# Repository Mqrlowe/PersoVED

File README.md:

# **Hello this is the ReadMe for my personnal github repo**

this repo contains mainly work for VED

### for the moment ts contains :
~~~
	PCB kicad projets
	CubeMx projetcs for the stm32
	A OneNote link to VED notes
~~~
### on the VED notes there is the following work :
~~~
	Can bus additionnal work to complete former studies
	regarding the can bus application in the FS architecture.
~~~

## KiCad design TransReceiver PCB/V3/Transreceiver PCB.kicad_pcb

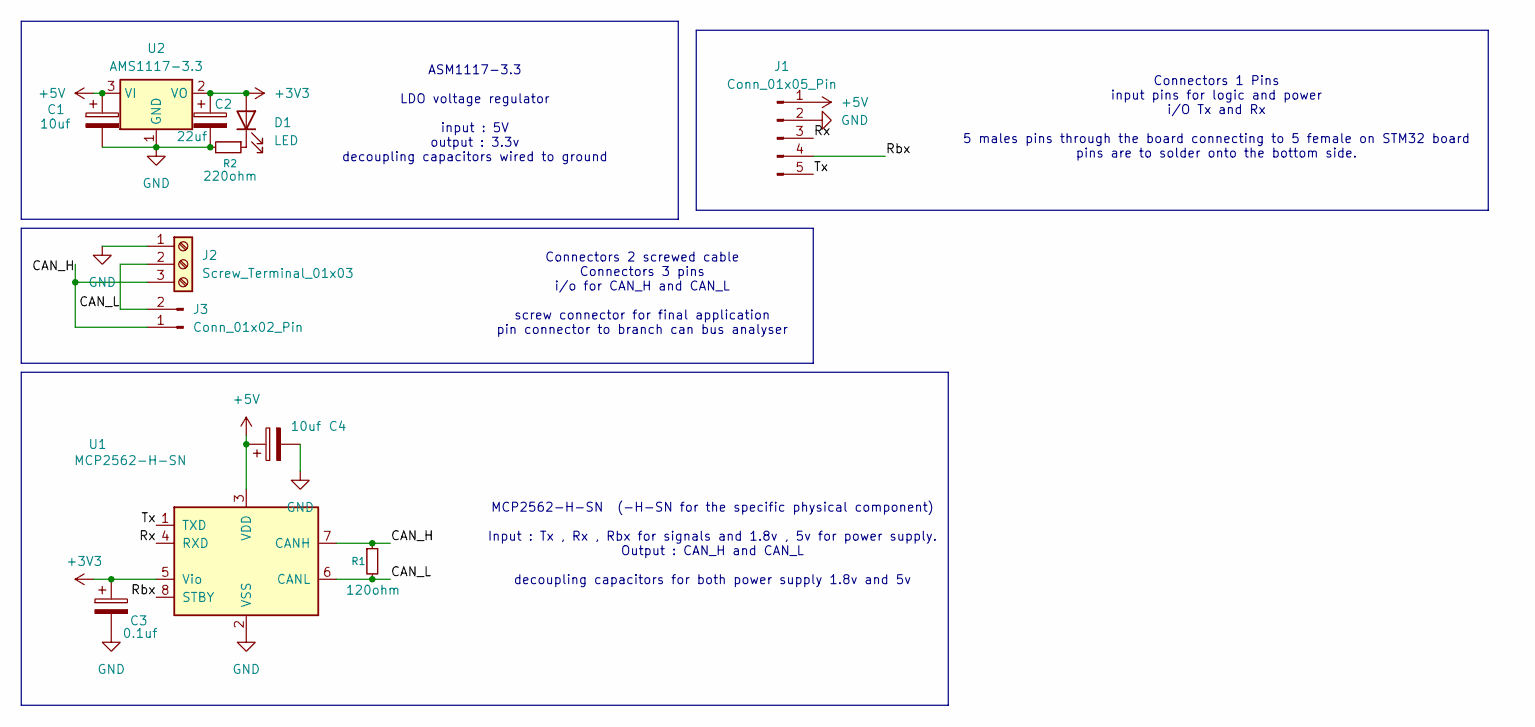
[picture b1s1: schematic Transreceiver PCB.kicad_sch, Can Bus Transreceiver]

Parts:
C1, C4: 10uf; C_0805_2012Metric
C2: 22uf; C_0805_2012Metric
C3: 0.1uf; C_0805_2012Metric
D1: LED; LED_0805_2012Metric
J1: Conn_01x05_Pin; PinHeader_1x05_P1.27mm_Horizontal
J2: Screw_Terminal_01x03; TerminalBlock_Phoenix_MKDS-1,5-3-5.08_1x03_P5.08mm_Horizont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
J3: Conn_01x02_Pin; PinHeader_1x02_P1.27mm_Vertical
R1: 120ohm; R_0805_2012Metric
R2: 220ohm; R_0805_2012Metric
U1: MCP2562-H-SN; SOIC-8_3.9x4.9mm_P1.27mm
U2: AMS1117-3.3; SOT-223-3_TabPin2

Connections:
+3V3: C2.1, C3.1, D1.2 (A), U1.5 (Vio), U2.2 (VO)
+5V: C1.1, C4.1, J1.1, U1.3 (VDD), U2.3 (VI)
/CAN_H: J2.3, J3.1, R1.1, U1.7 (CANH)
/CAN_L: J2.2, J3.2, R1.2, U1.6 (CANL)
/Rbx: J1.4, U1.8 (STBY)
/Rx: J1.3, U1.4 (RXD)
/Tx: J1.5, U1.1 (TXD)
GND: C1.2, C2.2, C3.2, C4.2, J1.2, J2.1, R2.2, U1.2 (VSS), U2.1 (GND)
unnamed: D1.1 (K), R2.1

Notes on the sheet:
ASM1117-3.3 LDO voltage regulator input : 5V output : 3.3v decoupling capacitors wired to ground
Connectors 2 screwed cable Connectors 3 pins i/o for CAN_H and CAN_L screw connector for final application pin connector to branch can bus analyser
MCP2562-H-SN (-H-SN for the specific physical component) Input : Tx , Rx , Rbx for signals and 1.8v , 5v for power supply. Output : CAN_H and CAN_L decoupling capacitors for both power supply 1.8v and 5v
Connectors 1 Pins input pins for logic and power i/O Tx and Rx 5 males pins through the board connecting to 5 female on STM32 board pins are to solder onto the bottom side.

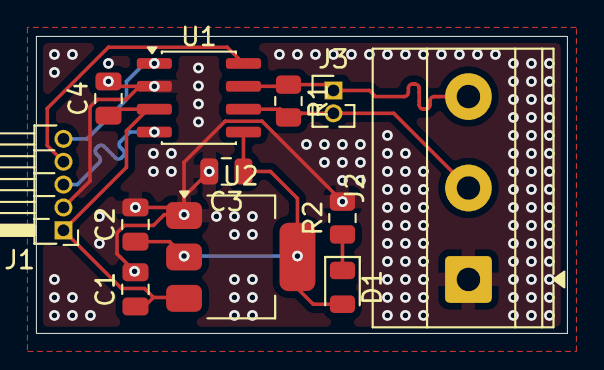
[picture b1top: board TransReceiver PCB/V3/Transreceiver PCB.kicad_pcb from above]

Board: 2 copper layers, 29.5 x 16.5 mm, 12 parts (0 on the bottom side), 9 nets.

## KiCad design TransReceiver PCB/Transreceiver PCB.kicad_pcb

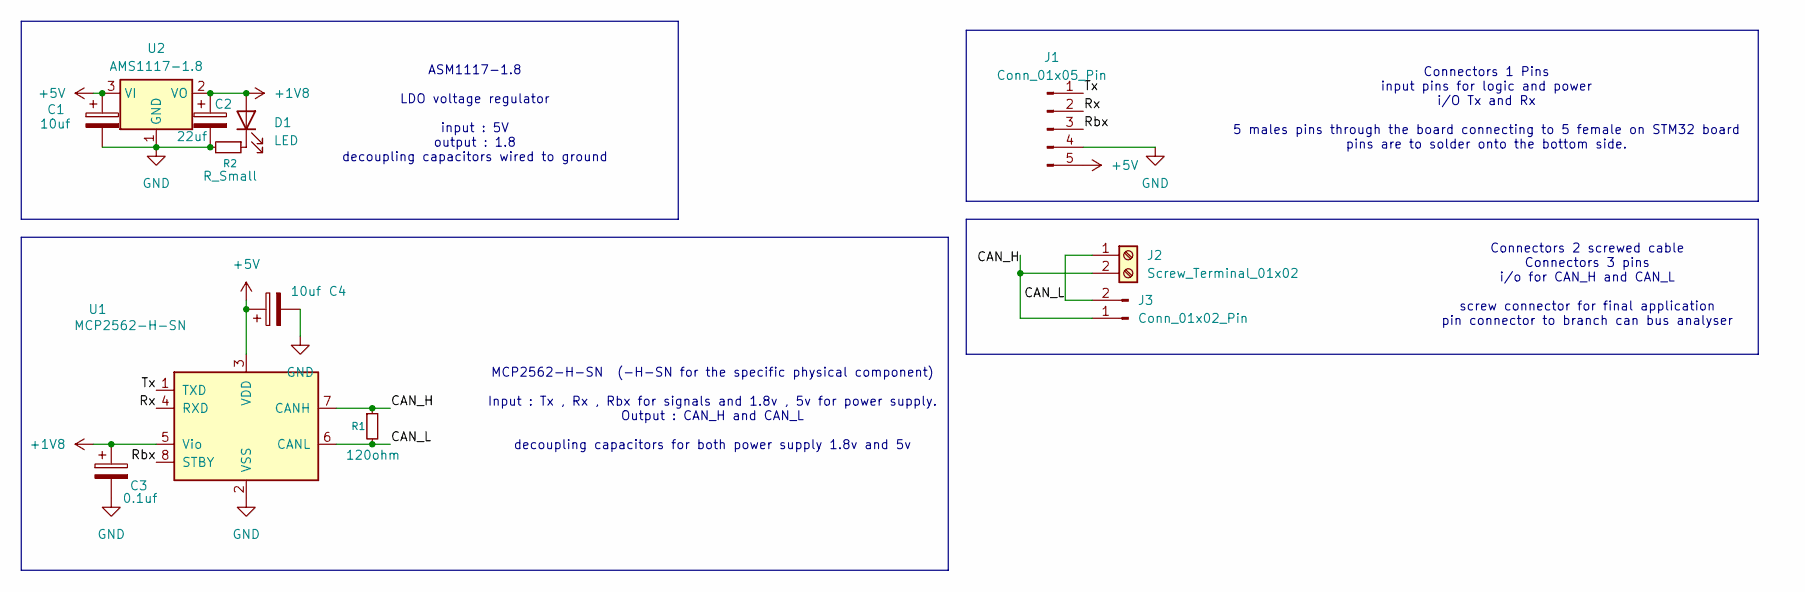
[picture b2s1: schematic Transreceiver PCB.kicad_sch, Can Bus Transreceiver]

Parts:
C1, C4: 10uf; C_0805_2012Metric
C2: 22uf; C_0805_2012Metric
C3: 0.1uf; C_0805_2012Metric
D1: LED; LED_0805_2012Metric
J1: Conn_01x05_Pin; PinHeader_1x05_P1.27mm_Vertical
J2: Screw_Terminal_01x02; TerminalBlock_Phoenix_PT-1,5-2-5.0-H_1x02_P5.00mm_Horizontal
J3: Conn_01x02_Pin; PinHeader_1x02_P1.27mm_Vertical
R1: 120ohm; R_0805_2012Metric
R2: R_Small; R_0805_2012Metric
U1: MCP2562-H-SN; SOIC-8_3.9x4.9mm_P1.27mm
U2: AMS1117-1.8; SOT-223-3_TabPin2

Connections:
+1V8: C2.1, C3.1, D1.2 (A), U1.5 (Vio), U2.2 (VO)
+5V: C1.1, C4.1, J1.5, U1.3 (VDD), U2.3 (VI)
/CAN_H: J2.2, J3.1, R1.1, U1.7 (CANH)
/CAN_L: J2.1, J3.2, R1.2, U1.6 (CANL)
/Rbx: J1.3, U1.8 (STBY)
/Rx: J1.2, U1.4 (RXD)
/Tx: J1.1, U1.1 (TXD)
GND: C1.2, C2.2, C3.2, C4.2, J1.4, R2.2, U1.2 (VSS), U2.1 (GND)
unnamed: D1.1 (K), R2.1

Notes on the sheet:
ASM1117-1.8 LDO voltage regulator input : 5V output : 1.8 decoupling capacitors wired to ground
Connectors 2 screwed cable Connectors 3 pins i/o for CAN_H and CAN_L screw connector for final application pin connector to branch can bus analyser
MCP2562-H-SN (-H-SN for the specific physical component) Input : Tx , Rx , Rbx for signals and 1.8v , 5v for power supply. Output : CAN_H and CAN_L decoupling capacitors for both power supply 1.8v and 5v
Connectors 1 Pins input pins for logic and power i/O Tx and Rx 5 males pins through the board connecting to 5 female on STM32 board pins are to solder onto the bottom side.

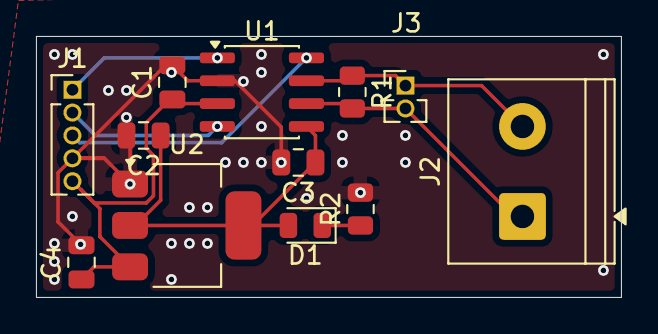
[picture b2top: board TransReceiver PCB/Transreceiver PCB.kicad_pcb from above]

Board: 2 copper layers, 32.5 x 14.5 mm, 12 parts (0 on the bottom side), 9 nets.
